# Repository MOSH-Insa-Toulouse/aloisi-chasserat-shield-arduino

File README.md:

# Shield Arduino pour capteur de gaz et communication LoRa

Ce projet fut réalisé dans le cadre de l'enseignement "Microcontrolleurs et Open-Source Hardware" de la 5e année "Innovative Smart Systems" à l'INSA de Toulouse. Nous avons conçu le PCB d'un shield Arduino permettant, une fois couplé à un Arduino UNO, de collecter les valeurs issues d'un capteur de gaz, et de les partager sur le réseau TTN (The Things Network) via une puce LoRa.

 *INSA Toulouse - Aloïsi Axelle & Chasserat Laurent - Novembre 2018 - 5 IR/ISS - Groupe B2*
  
# Fonctionnalités
Fonctionnalités du shield : 

-   Branchement du capteur de gaz (qui sera réalisé en salle blanche ultérieurement)

-   Circuit d’adaptation du signal issu du capteur pour l’envoyer vers l’ADC de l’Arduino UNO, implémentant notamment :
	-    2 types de filtrage :
			-   Filtrage des bruits :
				-   Filtrage passif à l’entrée du circuit pour couper les bruits HF
				-   Filtrage actif à l’aide de l’AOP LTC1050 pour plus d’efficacité
				-   Filtrage passif en sortie du circuit pour éliminer les bruits induits par celui-ci 
			-   Filtrage anti-repliement pour permettre l’échantillonnage par l’ADC
	-   La possibilité d’adapter le calibre, par le biais d’une résistance interchangeable    
	-   Une sortie vers l’ADC de l’Arduino UNO via la broche analogique A0
	
-   Intégration d’une puce de communication LoRa RN2483, pilotable par l’Arduino UNO, afin de permettre l’envoi des information issues du capteur au réseau TTN (The Things Network).

# Contenu

Ce projet KiCad contient le code source et les fichiers de conception du shield, à savoir :

-   La partie schématique, décrivant le circuit électronique implémenté (composants, routage des pins)    
-   La partie layout, décrivant la forme de la carte, l’emplacement des différents éléments sur celle-ci et la trajectoire des pistes de routage.

# Résultat obtenu

Conception du schematic :

Conception du layout :

Rendu 3D :

# Remarques et choix de conception

- Nous avons choisi de positionner notre Software Serial sur les Pins 7 et 8 pour répliquer la fonction de la communication série sur d'autres broches numériques de la carte.
- Nous avons transformé la forme du contour du shield en un rectangle plus grand que l'Arduino UNO pour faciliter le routage et l'inclusion de la puce LoRa.
- Au niveau du PCB, des avertissements de type "Pad près d'un pad" sont soulevés au moment de la vérification, car nous avons utilisé des modèles de résistances et de capacités choisis arbitrairement parmi les composants traversants, qui se sont avérés plus petits que ceux que nous utiliserons en réalité, et donc les marges de pistes que nous avons choisis pour l'impression du PCB réel se chevauchent. Pour changer cela, il faudrait choisir d'autres empreintes pour ces composants, ou réduire la taille des pads (ce qui n'est pas possible compte tenu des contraintes de fabrication qui nous sont imposées).
- Nous avons choisi d'implémenter toute la carte sur une seule couche de cuivre pour rendre possible sa fabrication à l'INSA. Les pistes sont sur la partie "Bottom" qui est aussi le plan de masse et les composants sont positionnés sur la partie "Top".

# Pistes d'amélioration

- Il pourrait être judicieux d'implémenter un système de recharge du capteur de gaz, permettant d'y appliquer une tension entre ses broches 3 et 4 lorsqu'il est saturé. Pour ce faire, nous pourrions par exemple utiliser un transistor pliloté à l'aide d'un bouton et d'une pin de l'Arduino Uno.

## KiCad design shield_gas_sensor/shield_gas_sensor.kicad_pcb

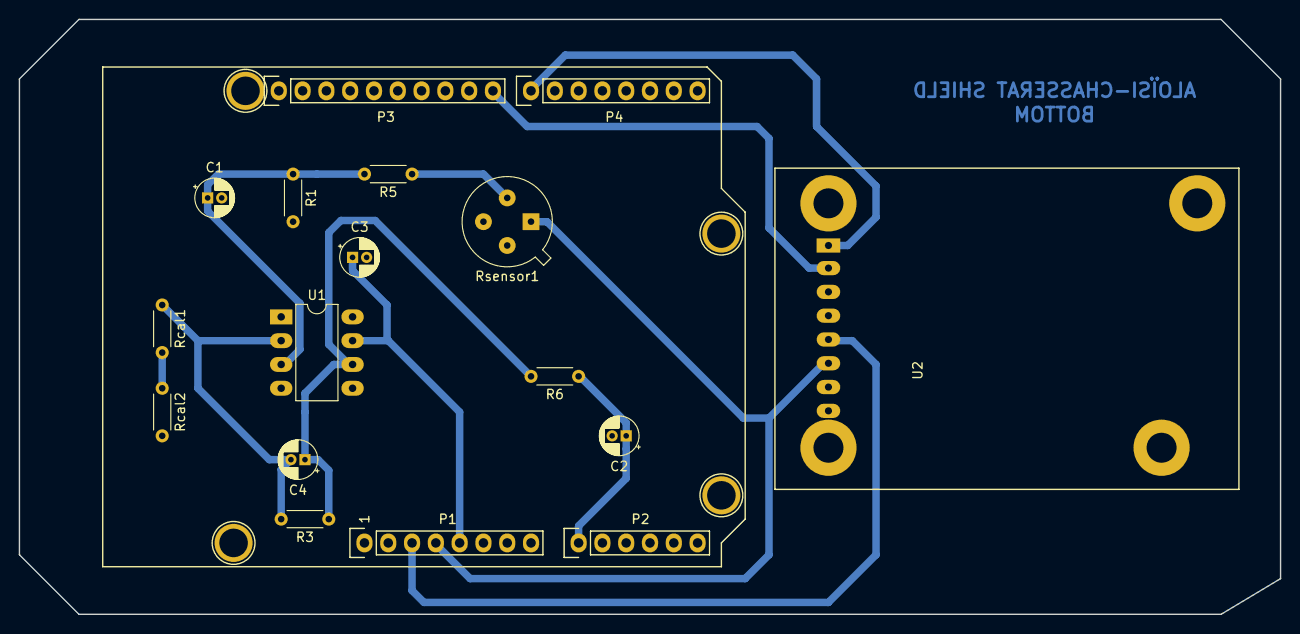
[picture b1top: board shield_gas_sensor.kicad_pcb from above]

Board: 2 copper layers, 134.6 x 63.5 mm, 21 parts (0 on the bottom side), 12 nets.

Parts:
C1, C2, C3: 100n; CP_Radial_D4.0mm_P1.50mm
C4: 1u; CP_Radial_D4.0mm_P1.50mm
P1: Power; Socket_Strip_Arduino_1x08
P2: Analog; Socket_Strip_Arduino_1x06
P3: Digital; Socket_Strip_Arduino_1x10
P4: Digital; Socket_Strip_Arduino_1x08
P5, P6, P7, P8: CONN_01X01; Arduino_1pin
R1, R3: 100k; R_Axial_DIN0204_L3.6mm_D1.6mm_P5.08mm_Horizontal
R5: 10k; R_Axial_DIN0204_L3.6mm_D1.6mm_P5.08mm_Horizontal
R6: 1k; R_Axial_DIN0204_L3.6mm_D1.6mm_P5.08mm_Horizontal
Rcal1, Rcal2: R; R_Axial_DIN0204_L3.6mm_D1.6mm_P5.08mm_Horizontal
Rsensor1: R; TO-5-4_cap_gaz
U1: LTC1050; DIP-8_W7.62mm_LongPads
U2: RN2483_Breakout; RN2483

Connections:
+3V3: P1.4, Rsensor1.1, U2.6
+5V: C3.1, P1.5, U1.7
/7: P4.1, U2.1
/8: P3.10, U2.2
/A0: C2.1, P2.1, R6.1
/Reset: P1.3, U2.5
GND: C1.2, C2.2, C3.2, P1.6, P1.7, P3.4, R1.2, Rcal2.2, U1.4, U2.8
unnamed: C1.1, R1.1, R5.2, U1.3
unnamed: C4.1, R3.1, R6.2, U1.6
unnamed: C4.2, R3.2, Rcal1.1, U1.2
unnamed: R5.1, Rsensor1.2
unnamed: Rcal1.2, Rcal2.1

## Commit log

2018-10-31 Début du projet
2018-10-31 Base Arduino Uno et Lib LTC1050
2018-10-31 Schema fini
2018-10-31 Association empreintes et netliste OK
2018-10-31 Placement composants
2018-10-31 Placement composants 2
2018-11-07 Ajout module LoRa empreintes et schematique
2018-11-12 fin de l'empreinte lora
2018-11-12 routes PCB
2018-11-12 Fin du PCB
2018-11-12 Update README end of project
2018-11-28 PCB Improvements for realisation at INSA
